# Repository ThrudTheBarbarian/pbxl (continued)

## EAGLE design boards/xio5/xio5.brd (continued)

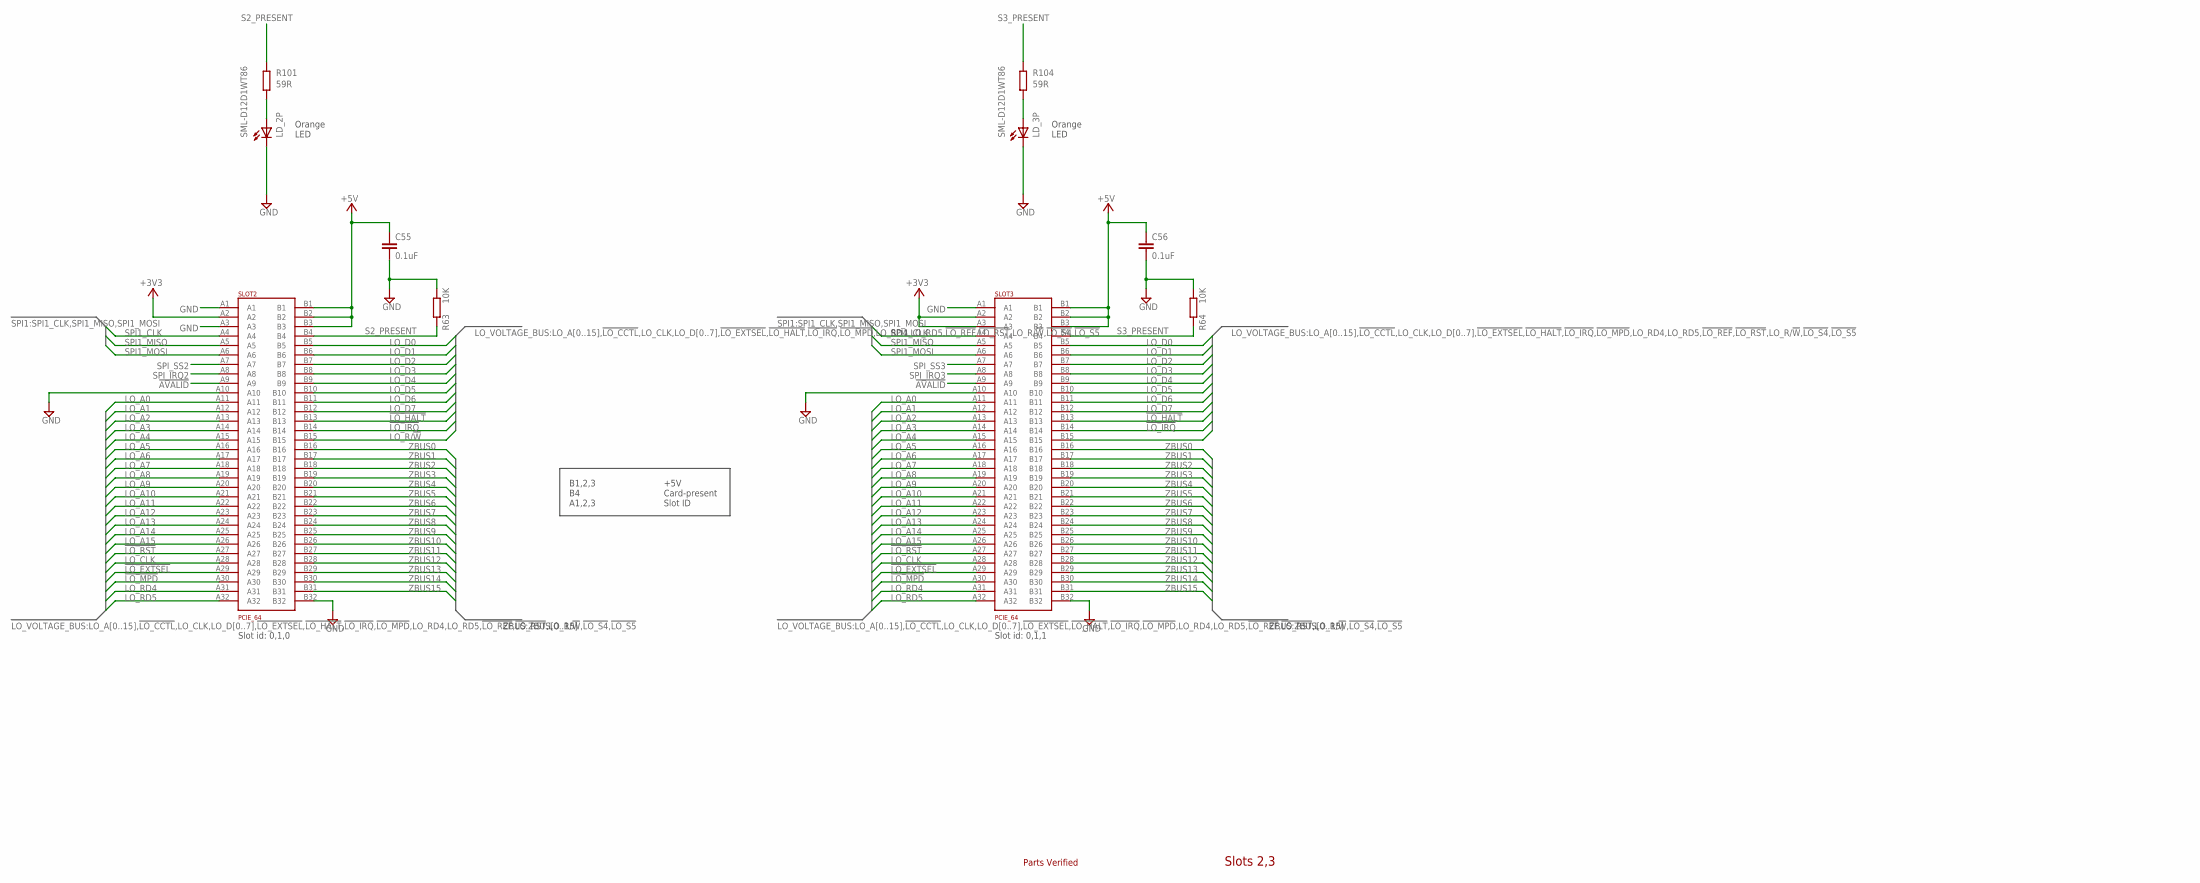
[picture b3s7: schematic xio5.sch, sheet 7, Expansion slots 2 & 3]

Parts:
C55, C56: 0.1uF; C0201
LD_2P, LD_3P: SML-D12D1WT86; CHIPLED_0603
R63, R64: 10K; R0201
R101, R104: 59R; R0402
SLOT2, SLOT3: PCIE_64; PCI-E_64

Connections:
!AVALID!: SLOT2.A9, SLOT3.A9; also elsewhere on the board
!LO_EXTSEL!: SLOT2.A29, SLOT3.A29; also elsewhere on the board
!LO_HALT!: SLOT2.B13, SLOT3.B13; also elsewhere on the board
!LO_IRQ!: SLOT2.B14, SLOT3.B14; also elsewhere on the board
!LO_MPD!: SLOT2.A30, SLOT3.A30; also elsewhere on the board
!LO_RST!: SLOT2.A27, SLOT3.A27; also elsewhere on the board
+3V3: SLOT2.A2, SLOT3.A2, SLOT3.A3; also elsewhere on the board
+5V: C55.1, C56.1, SLOT2.B1, SLOT2.B2, SLOT2.B3, SLOT3.B1, SLOT3.B2, SLOT3.B3; also elsewhere on the board
GND: C55.2, C56.2, LD_2P.C, LD_3P.C, R63.1, R64.1, SLOT2.A1, SLOT2.A3, SLOT2.A10, SLOT2.B32, SLOT3.A1, SLOT3.A10, SLOT3.B32; also elsewhere on the board
LO_A0: SLOT2.A11, SLOT3.A11; also elsewhere on the board
LO_A1: SLOT2.A12, SLOT3.A12; also elsewhere on the board
LO_A2: SLOT2.A13, SLOT3.A13; also elsewhere on the board
LO_A3: SLOT2.A14, SLOT3.A14; also elsewhere on the board
LO_A4: SLOT2.A15, SLOT3.A15; also elsewhere on the board
LO_A5: SLOT2.A16, SLOT3.A16; also elsewhere on the board
LO_A6: SLOT2.A17, SLOT3.A17; also elsewhere on the board
LO_A7: SLOT2.A18, SLOT3.A18; also elsewhere on the board
LO_A8: SLOT2.A19, SLOT3.A19; also elsewhere on the board
LO_A9: SLOT2.A20, SLOT3.A20; also elsewhere on the board
LO_A10: SLOT2.A21, SLOT3.A21; also elsewhere on the board
LO_A11: SLOT2.A22, SLOT3.A22; also elsewhere on the board
LO_A12: SLOT2.A23, SLOT3.A23; also elsewhere on the board
LO_A13: SLOT2.A24, SLOT3.A24; also elsewhere on the board
LO_A14: SLOT2.A25, SLOT3.A25; also elsewhere on the board
LO_A15: SLOT2.A26, SLOT3.A26; also elsewhere on the board
LO_CLK: SLOT2.A28, SLOT3.A28; also elsewhere on the board
LO_D0: SLOT2.B5, SLOT3.B5; also elsewhere on the board
LO_D1: SLOT2.B6, SLOT3.B6; also elsewhere on the board
LO_D2: SLOT2.B7, SLOT3.B7; also elsewhere on the board
LO_D3: SLOT2.B8, SLOT3.B8; also elsewhere on the board
LO_D4: SLOT2.B9, SLOT3.B9; also elsewhere on the board
LO_D5: SLOT2.B10, SLOT3.B10; also elsewhere on the board
LO_D6: SLOT2.B11, SLOT3.B11; also elsewhere on the board
LO_D7: SLOT2.B12, SLOT3.B12; also elsewhere on the board
LO_R/!W!: SLOT2.B15, SLOT3.B15; also elsewhere on the board
LO_RD4: SLOT2.A31, SLOT3.A31; also elsewhere on the board
LO_RD5: SLOT2.A32, SLOT3.A32; also elsewhere on the board
unnamed: LD_2P.A, R101.2
unnamed: LD_3P.A, R104.2
S2_PRESENT: R63.2, R101.1, SLOT2.B4; also elsewhere on the board
S3_PRESENT: R64.2, R104.1, SLOT3.B4; also elsewhere on the board
SPI1_CLK: SLOT2.A4, SLOT3.A4; also elsewhere on the board
SPI1_MISO: SLOT2.A5, SLOT3.A5; also elsewhere on the board
SPI1_MOSI: SLOT2.A6, SLOT3.A6; also elsewhere on the board
SPI_IRQ2: SLOT2.A8; also elsewhere on the board
SPI_IRQ3: SLOT3.A8; also elsewhere on the board
SPI_SS2: SLOT2.A7; also elsewhere on the board
SPI_SS3: SLOT3.A7; also elsewhere on the board
ZBUS0: SLOT2.B16, SLOT3.B16; also elsewhere on the board
ZBUS1: SLOT2.B17, SLOT3.B17; also elsewhere on the board
ZBUS2: SLOT2.B18, SLOT3.B18; also elsewhere on the board
ZBUS3: SLOT2.B19, SLOT3.B19; also elsewhere on the board
ZBUS4: SLOT2.B20, SLOT3.B20; also elsewhere on the board
ZBUS5: SLOT2.B21, SLOT3.B21; also elsewhere on the board
ZBUS6: SLOT2.B22, SLOT3.B22; also elsewhere on the board
ZBUS7: SLOT2.B23, SLOT3.B23; also elsewhere on the board
ZBUS8: SLOT2.B24, SLOT3.B24; also elsewhere on the board
ZBUS9: SLOT2.B25, SLOT3.B25; also elsewhere on the board
ZBUS10: SLOT2.B26, SLOT3.B26; also elsewhere on the board
ZBUS11: SLOT2.B27, SLOT3.B27; also elsewhere on the board
ZBUS12: SLOT2.B28, SLOT3.B28; also elsewhere on the board
ZBUS13: SLOT2.B29, SLOT3.B29; also elsewhere on the board
ZBUS14: SLOT2.B30, SLOT3.B30; also elsewhere on the board
ZBUS15: SLOT2.B31, SLOT3.B31; also elsewhere on the board

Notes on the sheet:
Slots 2,3
Slot id: 0,1,0
Slot id: 0,1,1
B1,2,3 B4 A1,2,3
+5V Card-present Slot ID
Orange LED
Parts Verified

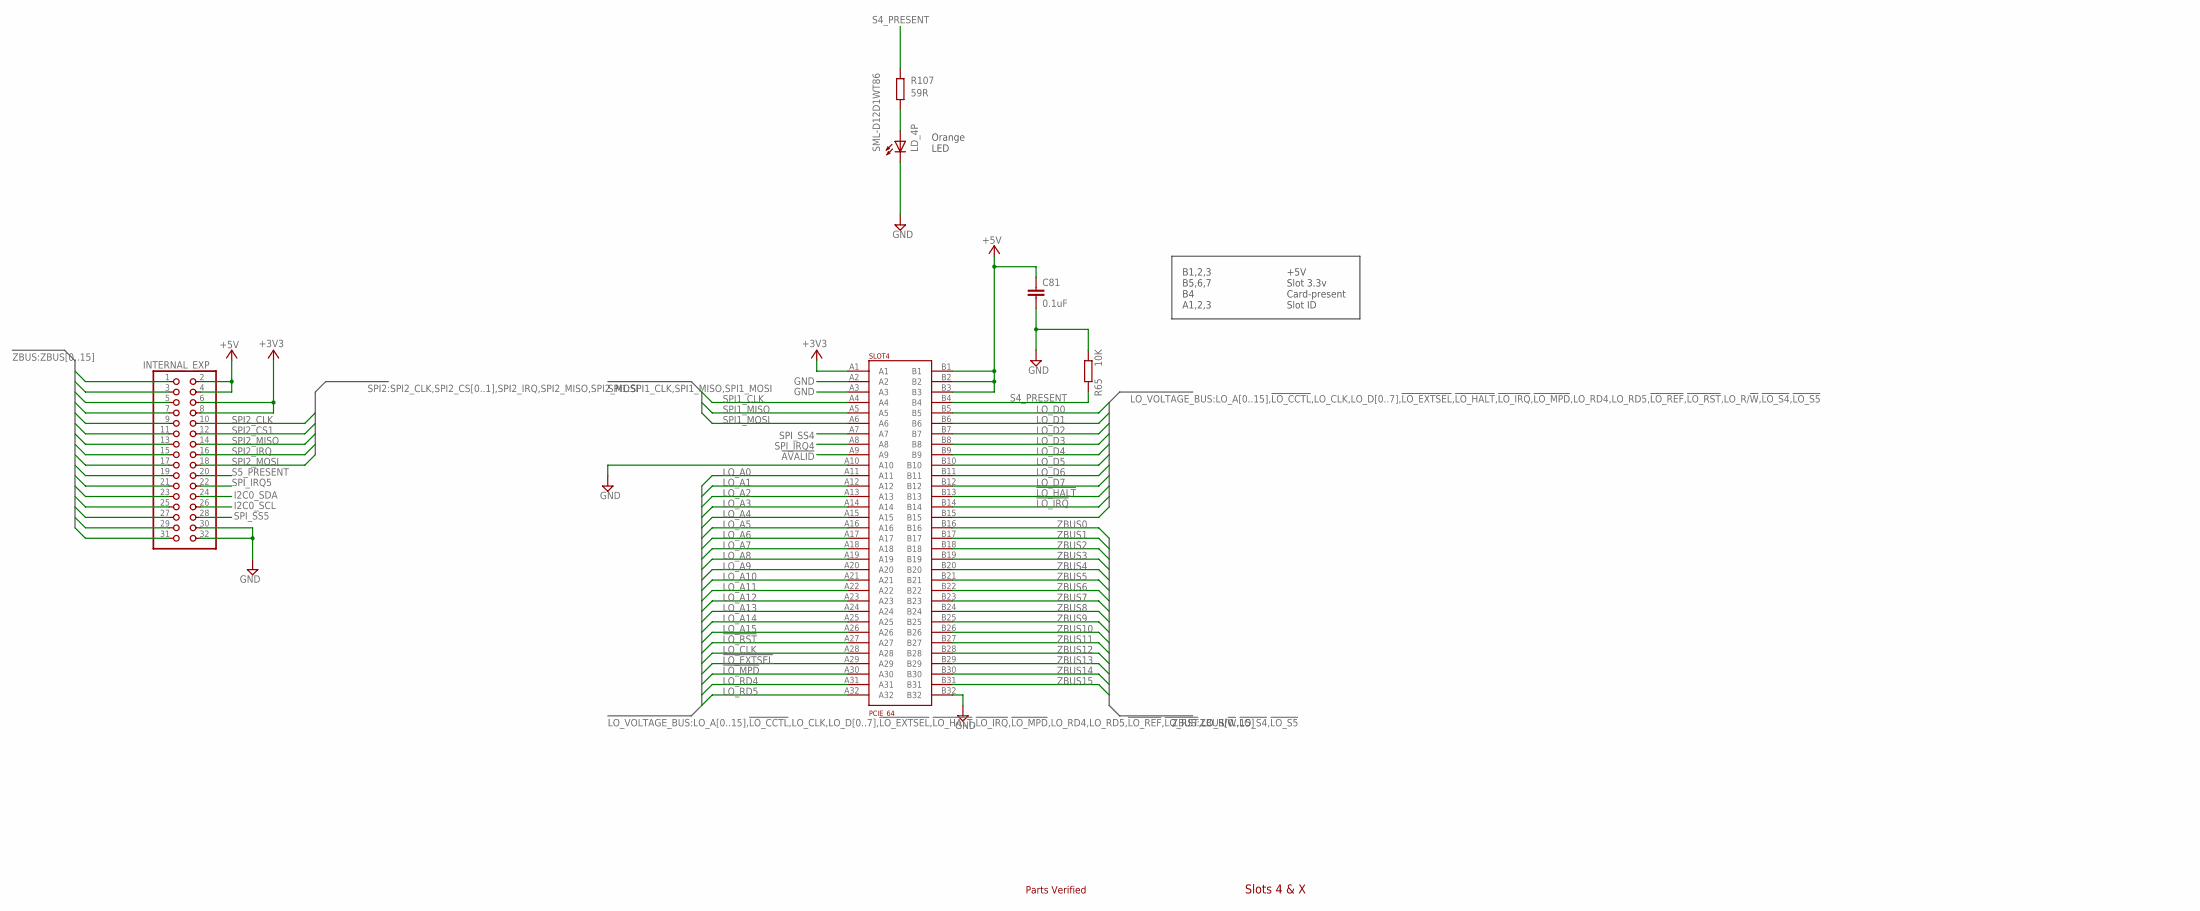
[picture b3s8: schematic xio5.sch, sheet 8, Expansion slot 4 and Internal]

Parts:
C81: 0.1uF; C0201
INTERNAL_EXP: PINHD-2X16_2.00; 2X16M
LD_4P: SML-D12D1WT86; CHIPLED_0603
R65: 10K; R0201
R107: 59R; R0402
SLOT4: PCIE_64; PCI-E_64

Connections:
!AVALID!: SLOT4.A9; also elsewhere on the board
!LO_EXTSEL!: SLOT4.A29; also elsewhere on the board
!LO_HALT!: SLOT4.B13; also elsewhere on the board
!LO_IRQ!: SLOT4.B14; also elsewhere on the board
!LO_MPD!: SLOT4.A30; also elsewhere on the board
!LO_RST!: SLOT4.A27; also elsewhere on the board
+3V3: INTERNAL_EXP.6, INTERNAL_EXP.8, SLOT4.A1; also elsewhere on the board
+5V: C81.1, INTERNAL_EXP.2, INTERNAL_EXP.4, SLOT4.B1, SLOT4.B2, SLOT4.B3; also elsewhere on the board
GND: C81.2, INTERNAL_EXP.30, INTERNAL_EXP.32, LD_4P.C, R65.1, SLOT4.A2, SLOT4.A3, SLOT4.A10, SLOT4.B32; also elsewhere on the board
I2C0_SCL: INTERNAL_EXP.26; also elsewhere on the board
I2C0_SDA: INTERNAL_EXP.24; also elsewhere on the board
LO_A0: SLOT4.A11; also elsewhere on the board
LO_A1: SLOT4.A12; also elsewhere on the board
LO_A2: SLOT4.A13; also elsewhere on the board
LO_A3: SLOT4.A14; also elsewhere on the board
LO_A4: SLOT4.A15; also elsewhere on the board
LO_A5: SLOT4.A16; also elsewhere on the board
LO_A6: SLOT4.A17; also elsewhere on the board
LO_A7: SLOT4.A18; also elsewhere on the board
LO_A8: SLOT4.A19; also elsewhere on the board
LO_A9: SLOT4.A20; also elsewhere on the board
LO_A10: SLOT4.A21; also elsewhere on the board
LO_A11: SLOT4.A22; also elsewhere on the board
LO_A12: SLOT4.A23; also elsewhere on the board
LO_A13: SLOT4.A24; also elsewhere on the board
LO_A14: SLOT4.A25; also elsewhere on the board
LO_A15: SLOT4.A26; also elsewhere on the board
LO_CLK: SLOT4.A28; also elsewhere on the board
LO_D0: SLOT4.B5; also elsewhere on the board
LO_D1: SLOT4.B6; also elsewhere on the board
LO_D2: SLOT4.B7; also elsewhere on the board
LO_D3: SLOT4.B8; also elsewhere on the board
LO_D4: SLOT4.B9; also elsewhere on the board
LO_D5: SLOT4.B10; also elsewhere on the board
LO_D6: SLOT4.B11; also elsewhere on the board
LO_D7: SLOT4.B12; also elsewhere on the board
LO_R/!W!: SLOT4.B15; also elsewhere on the board
LO_RD4: SLOT4.A31; also elsewhere on the board
LO_RD5: SLOT4.A32; also elsewhere on the board
unnamed: LD_4P.A, R107.2
S4_PRESENT: R65.2, R107.1, SLOT4.B4; also elsewhere on the board
S5_PRESENT: INTERNAL_EXP.20; also elsewhere on the board
SPI1_CLK: SLOT4.A4; also elsewhere on the board
SPI1_MISO: SLOT4.A5; also elsewhere on the board
SPI1_MOSI: SLOT4.A6; also elsewhere on the board
SPI2_CLK: INTERNAL_EXP.10; also elsewhere on the board
SPI2_CS1: INTERNAL_EXP.12; also elsewhere on the board
SPI2_IRQ: INTERNAL_EXP.16; also elsewhere on the board
SPI2_MISO: INTERNAL_EXP.14; also elsewhere on the board
SPI2_MOSI: INTERNAL_EXP.18; also elsewhere on the board
SPI_IRQ4: SLOT4.A8; also elsewhere on the board
SPI_IRQ5: INTERNAL_EXP.22; also elsewhere on the board
SPI_SS4: SLOT4.A7; also elsewhere on the board
SPI_SS5: INTERNAL_EXP.28; also elsewhere on the board
ZBUS0: INTERNAL_EXP.31, SLOT4.B16; also elsewhere on the board
ZBUS1: INTERNAL_EXP.29, SLOT4.B17; also elsewhere on the board
ZBUS2: INTERNAL_EXP.27, SLOT4.B18; also elsewhere on the board
ZBUS3: INTERNAL_EXP.25, SLOT4.B19; also elsewhere on the board
ZBUS4: INTERNAL_EXP.23, SLOT4.B20; also elsewhere on the board
ZBUS5: INTERNAL_EXP.21, SLOT4.B21; also elsewhere on the board
ZBUS6: INTERNAL_EXP.19, SLOT4.B22; also elsewhere on the board
ZBUS7: INTERNAL_EXP.17, SLOT4.B23; also elsewhere on the board
ZBUS8: INTERNAL_EXP.15, SLOT4.B24; also elsewhere on the board
ZBUS9: INTERNAL_EXP.13, SLOT4.B25; also elsewhere on the board
ZBUS10: INTERNAL_EXP.11, SLOT4.B26; also elsewhere on the board
ZBUS11: INTERNAL_EXP.9, SLOT4.B27; also elsewhere on the board
ZBUS12: INTERNAL_EXP.7, SLOT4.B28; also elsewhere on the board
ZBUS13: INTERNAL_EXP.5, SLOT4.B29; also elsewhere on the board
ZBUS14: INTERNAL_EXP.3, SLOT4.B30; also elsewhere on the board
ZBUS15: INTERNAL_EXP.1, SLOT4.B31; also elsewhere on the board

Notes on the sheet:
Slots 4 & X
B1,2,3 B5,6,7 B4 A1,2,3
+5V Slot 3.3v Card-present Slot ID
Orange LED
Parts Verified

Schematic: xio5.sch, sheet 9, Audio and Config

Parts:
AUDIO_CONN: PINHD-2X06_2.00; 2X06M
R7, R8, R9, R11, R12, R14, R18, R20: 10K; R0201
SW_CONFIG: SW_DIP-8; DIPSWITCH-08
ZTURN: ZTURN

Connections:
+3V3: AUDIO_CONN.7, R7.2, R8.2, R9.2, R11.2, R12.2, R14.2, R18.2, R20.2; also elsewhere on the board
+5V: AUDIO_CONN.5; also elsewhere on the board
CFG0: R14.1, SW_CONFIG.1; also elsewhere on the board
CFG1: R12.1, SW_CONFIG.2; also elsewhere on the board
CFG2: R11.1, SW_CONFIG.3; also elsewhere on the board
CFG3: R9.1, SW_CONFIG.4; also elsewhere on the board
CFG4: R8.1, SW_CONFIG.5; also elsewhere on the board
CFG5: R7.1, SW_CONFIG.6; also elsewhere on the board
CFG6: R18.1, SW_CONFIG.7; also elsewhere on the board
CFG7: R20.1, SW_CONFIG.8; also elsewhere on the board
GND: AUDIO_CONN.4, AUDIO_CONN.9, AUDIO_CONN.11, SW_CONFIG.9, SW_CONFIG.10, SW_CONFIG.11, SW_CONFIG.12, SW_CONFIG.13, SW_CONFIG.14, SW_CONFIG.15, SW_CONFIG.16; also elsewhere on the board
I2C0_SCL: AUDIO_CONN.1, ZTURN.CN1_78 (I2C0_SCL); also elsewhere on the board
I2C0_SDA: AUDIO_CONN.3, ZTURN.CN1_76 (I2C0_SDA); also elsewhere on the board
unnamed: AUDIO_CONN.2, ZTURN.CN1_71 (I2S_SCLK)
unnamed: AUDIO_CONN.12, ZTURN.CN1_72 (I2S_FSYNC_OUT)
unnamed: AUDIO_CONN.10, ZTURN.CN1_74 (I2S_DOUT)
unnamed: AUDIO_CONN.8, ZTURN.CN1_73 (I2S_FSYNC_IN)
unnamed: AUDIO_CONN.6, ZTURN.CN1_75 (I2S_DIN)

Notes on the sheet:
Audio and config
Parts Verified

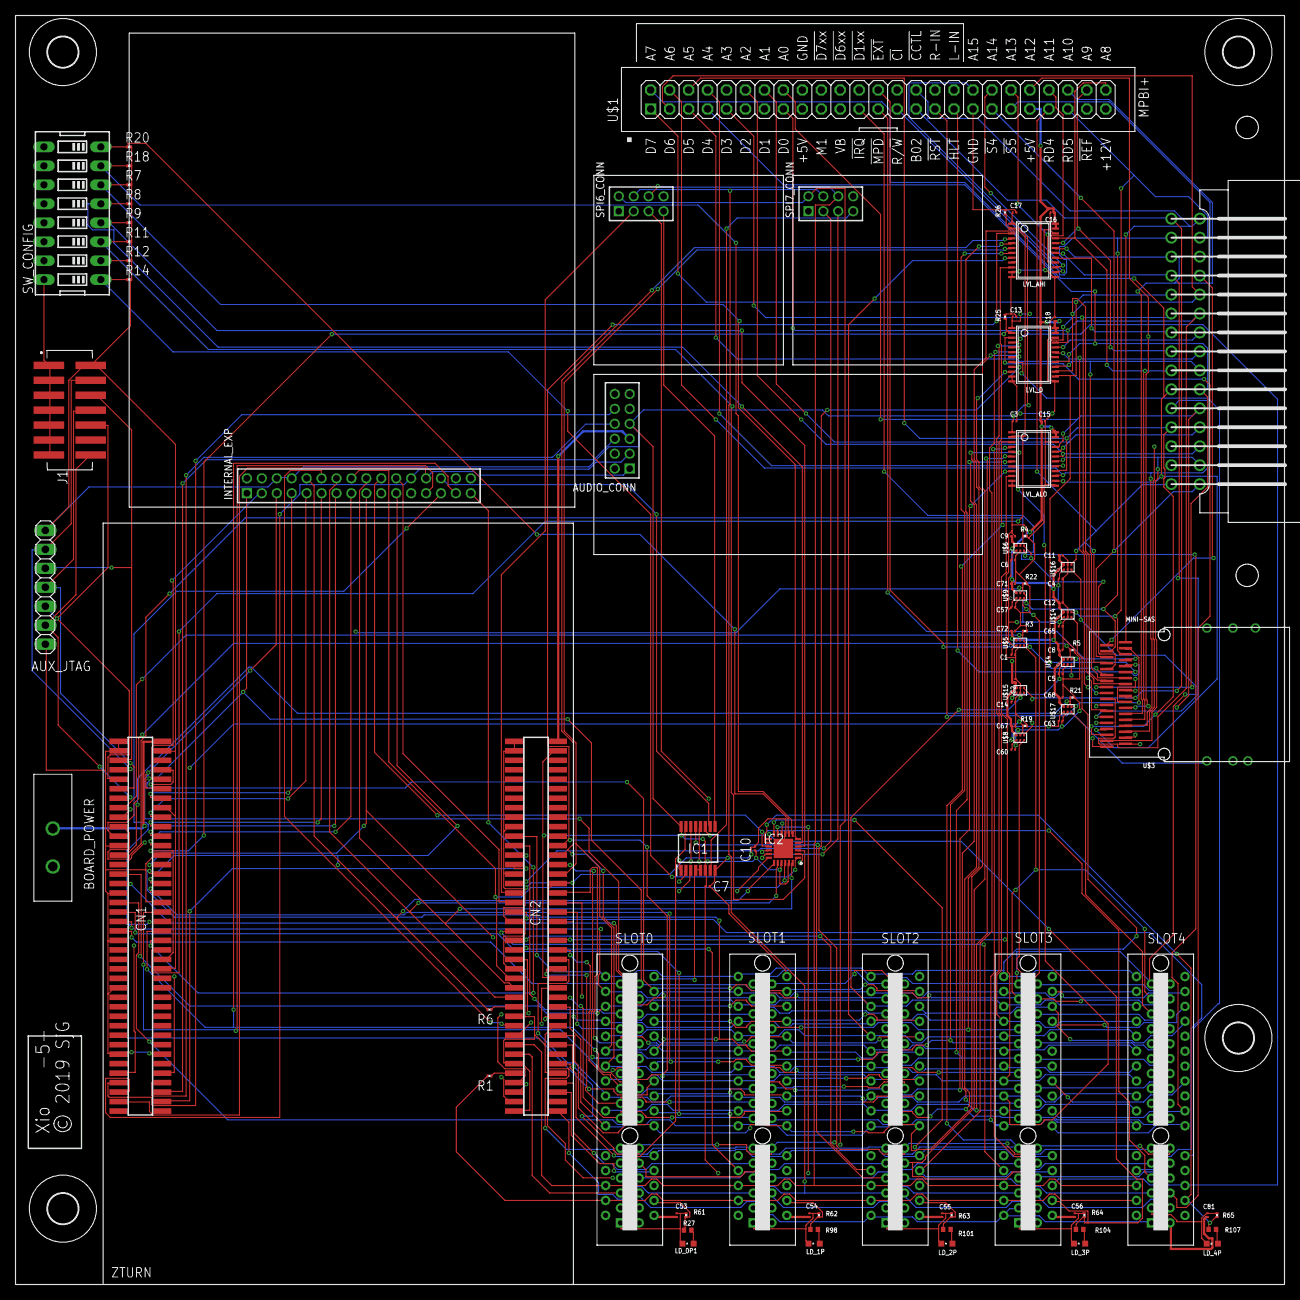
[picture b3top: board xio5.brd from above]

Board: 6 copper layers, 170.0 x 170.0 mm, 99 parts (0 on the bottom side), 161 nets.

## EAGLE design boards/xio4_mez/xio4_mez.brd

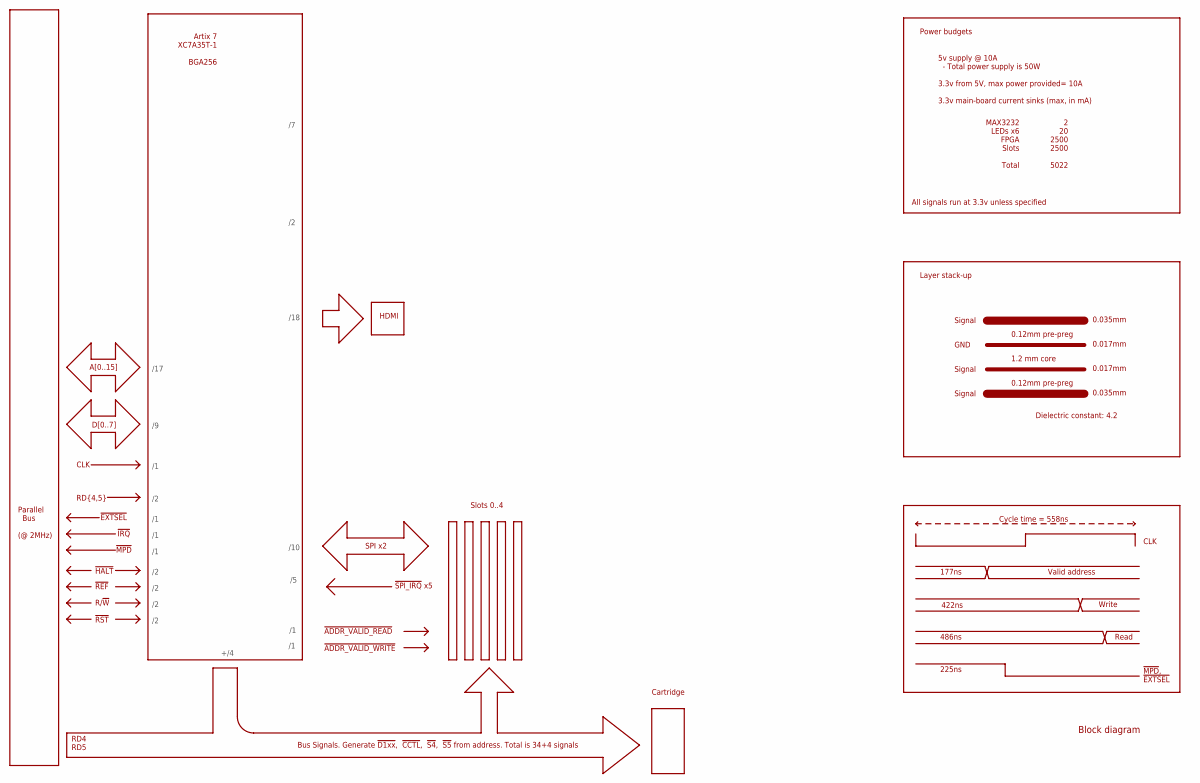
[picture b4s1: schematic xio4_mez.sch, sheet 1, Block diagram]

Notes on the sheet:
Slots 0..4
Bus Signals. Generate !D1xx!, !CCTL!, !S4!, !S5! from address. Total is 34+4 signals
5v supply @ 10A - Total power supply is 50W 3.3v from 5V, max power provided= 10A 3.3v main-board current sinks (max, in mA)
MAX3232 LEDs x6 FPGA Slots Total
2 20 2500 2500 5022
1.2 mm core
0.12mm pre-preg
0.035mm
0.017mm
Layer stack-up
GND
Dielectric constant: 4.2
Cycle time = 558ns
Valid address
Write
Read
177ns
422ns
486ns
225ns
!MPD!, !EXTSEL!
CLK
Power budgets
Artix 7 XC7A35T-1 BGA256
HDMI
Signal
Block diagram
Parallel Bus (@ 2MHz)
A[0..15]
D[0..7]
RD{4,5}
!MPD!
!IRQ!
!EXTSEL!
!HALT!
!REF!
R/!W!
/17
!ADDR_VALID_READ!
!ADDR_VALID_WRITE!

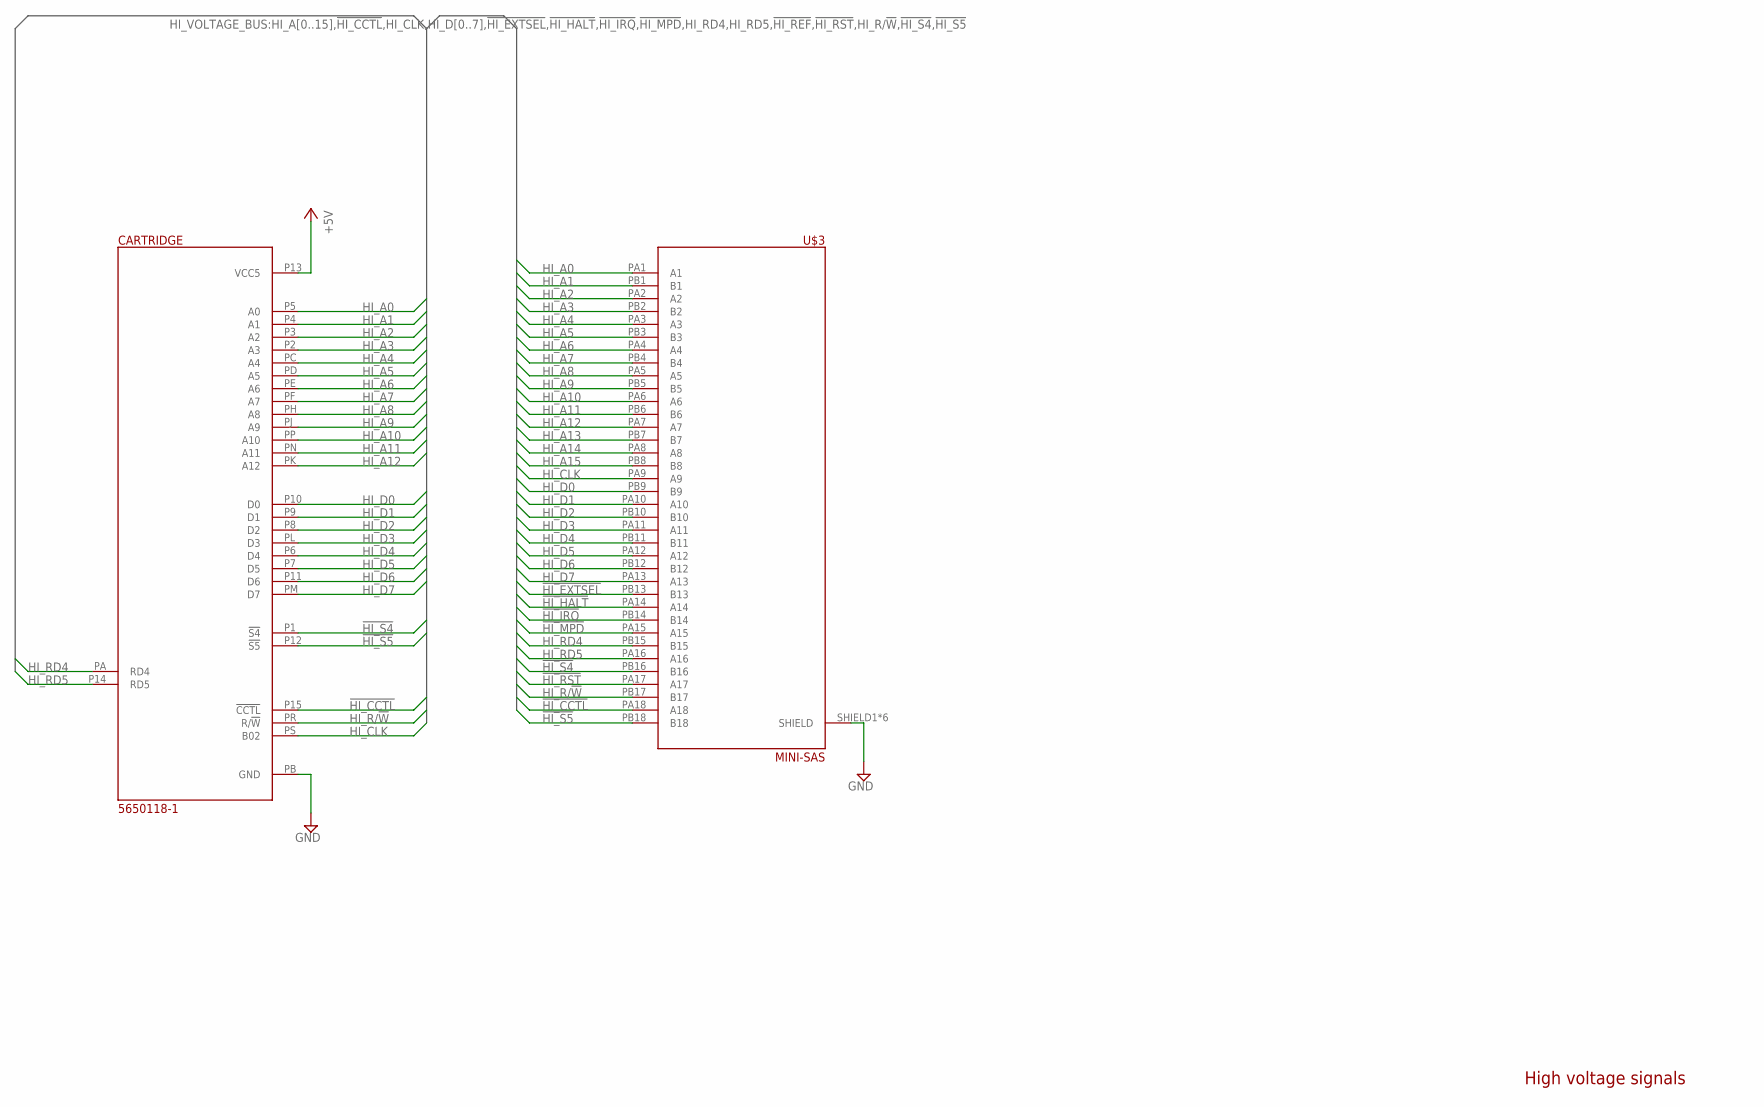
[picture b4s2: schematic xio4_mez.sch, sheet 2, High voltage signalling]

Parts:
CARTRIDGE: 5650118-1; A8_CART
U$3: MINI-SAS

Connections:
!HI_CCTL!: CARTRIDGE.P15 (!CCTL!), U$3.PA18 (A18)
!HI_EXTSEL!: U$3.PB13 (B13); also elsewhere on the board
!HI_HALT!: U$3.PA14 (A14); also elsewhere on the board
!HI_IRQ!: U$3.PB14 (B14); also elsewhere on the board
!HI_MPD!: U$3.PA15 (A15); also elsewhere on the board
!HI_RST!: U$3.PA17 (A17); also elsewhere on the board
!HI_S4!: CARTRIDGE.P1 (!S4!), U$3.PB16 (B16)
!HI_S5!: CARTRIDGE.P12 (!S5!), U$3.PB18 (B18)
+5V: CARTRIDGE.P13 (VCC5); also elsewhere on the board
GND: CARTRIDGE.PB (GND), U$3.SHIELD1 (SHIELD), U$3.SHIELD2 (SHIELD), U$3.SHIELD3 (SHIELD), U$3.SHIELD4 (SHIELD), U$3.SHIELD5 (SHIELD), U$3.SHIELD6 (SHIELD); also elsewhere on the board
HI_A0: CARTRIDGE.P5 (A0), U$3.PA1 (A1); also elsewhere on the board
HI_A1: CARTRIDGE.P4 (A1), U$3.PB1 (B1); also elsewhere on the board
HI_A2: CARTRIDGE.P3 (A2), U$3.PA2 (A2); also elsewhere on the board
HI_A3: CARTRIDGE.P2 (A3), U$3.PB2 (B2); also elsewhere on the board
HI_A4: CARTRIDGE.PC (A4), U$3.PA3 (A3); also elsewhere on the board
HI_A5: CARTRIDGE.PD (A5), U$3.PB3 (B3); also elsewhere on the board
HI_A6: CARTRIDGE.PE (A6), U$3.PA4 (A4); also elsewhere on the board
HI_A7: CARTRIDGE.PF (A7), U$3.PB4 (B4); also elsewhere on the board
HI_A8: CARTRIDGE.PH (A8), U$3.PA5 (A5); also elsewhere on the board
HI_A9: CARTRIDGE.PJ (A9), U$3.PB5 (B5); also elsewhere on the board
HI_A10: CARTRIDGE.PP (A10), U$3.PA6 (A6); also elsewhere on the board
HI_A11: CARTRIDGE.PN (A11), U$3.PB6 (B6); also elsewhere on the board
HI_A12: CARTRIDGE.PK (A12), U$3.PA7 (A7); also elsewhere on the board
HI_A13: U$3.PB7 (B7); also elsewhere on the board
HI_A14: U$3.PA8 (A8); also elsewhere on the board
HI_A15: U$3.PB8 (B8); also elsewhere on the board
HI_CLK: CARTRIDGE.PS (B02), U$3.PA9 (A9); also elsewhere on the board
HI_D0: CARTRIDGE.P10 (D0), U$3.PB9 (B9); also elsewhere on the board
HI_D1: CARTRIDGE.P9 (D1), U$3.PA10 (A10); also elsewhere on the board
HI_D2: CARTRIDGE.P8 (D2), U$3.PB10 (B10); also elsewhere on the board
HI_D3: CARTRIDGE.PL (D3), U$3.PA11 (A11); also elsewhere on the board
HI_D4: CARTRIDGE.P6 (D4), U$3.PB11 (B11); also elsewhere on the board
HI_D5: CARTRIDGE.P7 (D5), U$3.PA12 (A12); also elsewhere on the board
HI_D6: CARTRIDGE.P11 (D6), U$3.PB12 (B12); also elsewhere on the board
HI_D7: CARTRIDGE.PM (D7), U$3.PA13 (A13); also elsewhere on the board
HI_R/!W!: CARTRIDGE.PR (R/!W!), U$3.PB17 (B17); also elsewhere on the board
HI_RD4: CARTRIDGE.PA (RD4), U$3.PB15 (B15); also elsewhere on the board
HI_RD5: CARTRIDGE.P14 (RD5), U$3.PA16 (A16); also elsewhere on the board

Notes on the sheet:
High voltage signals

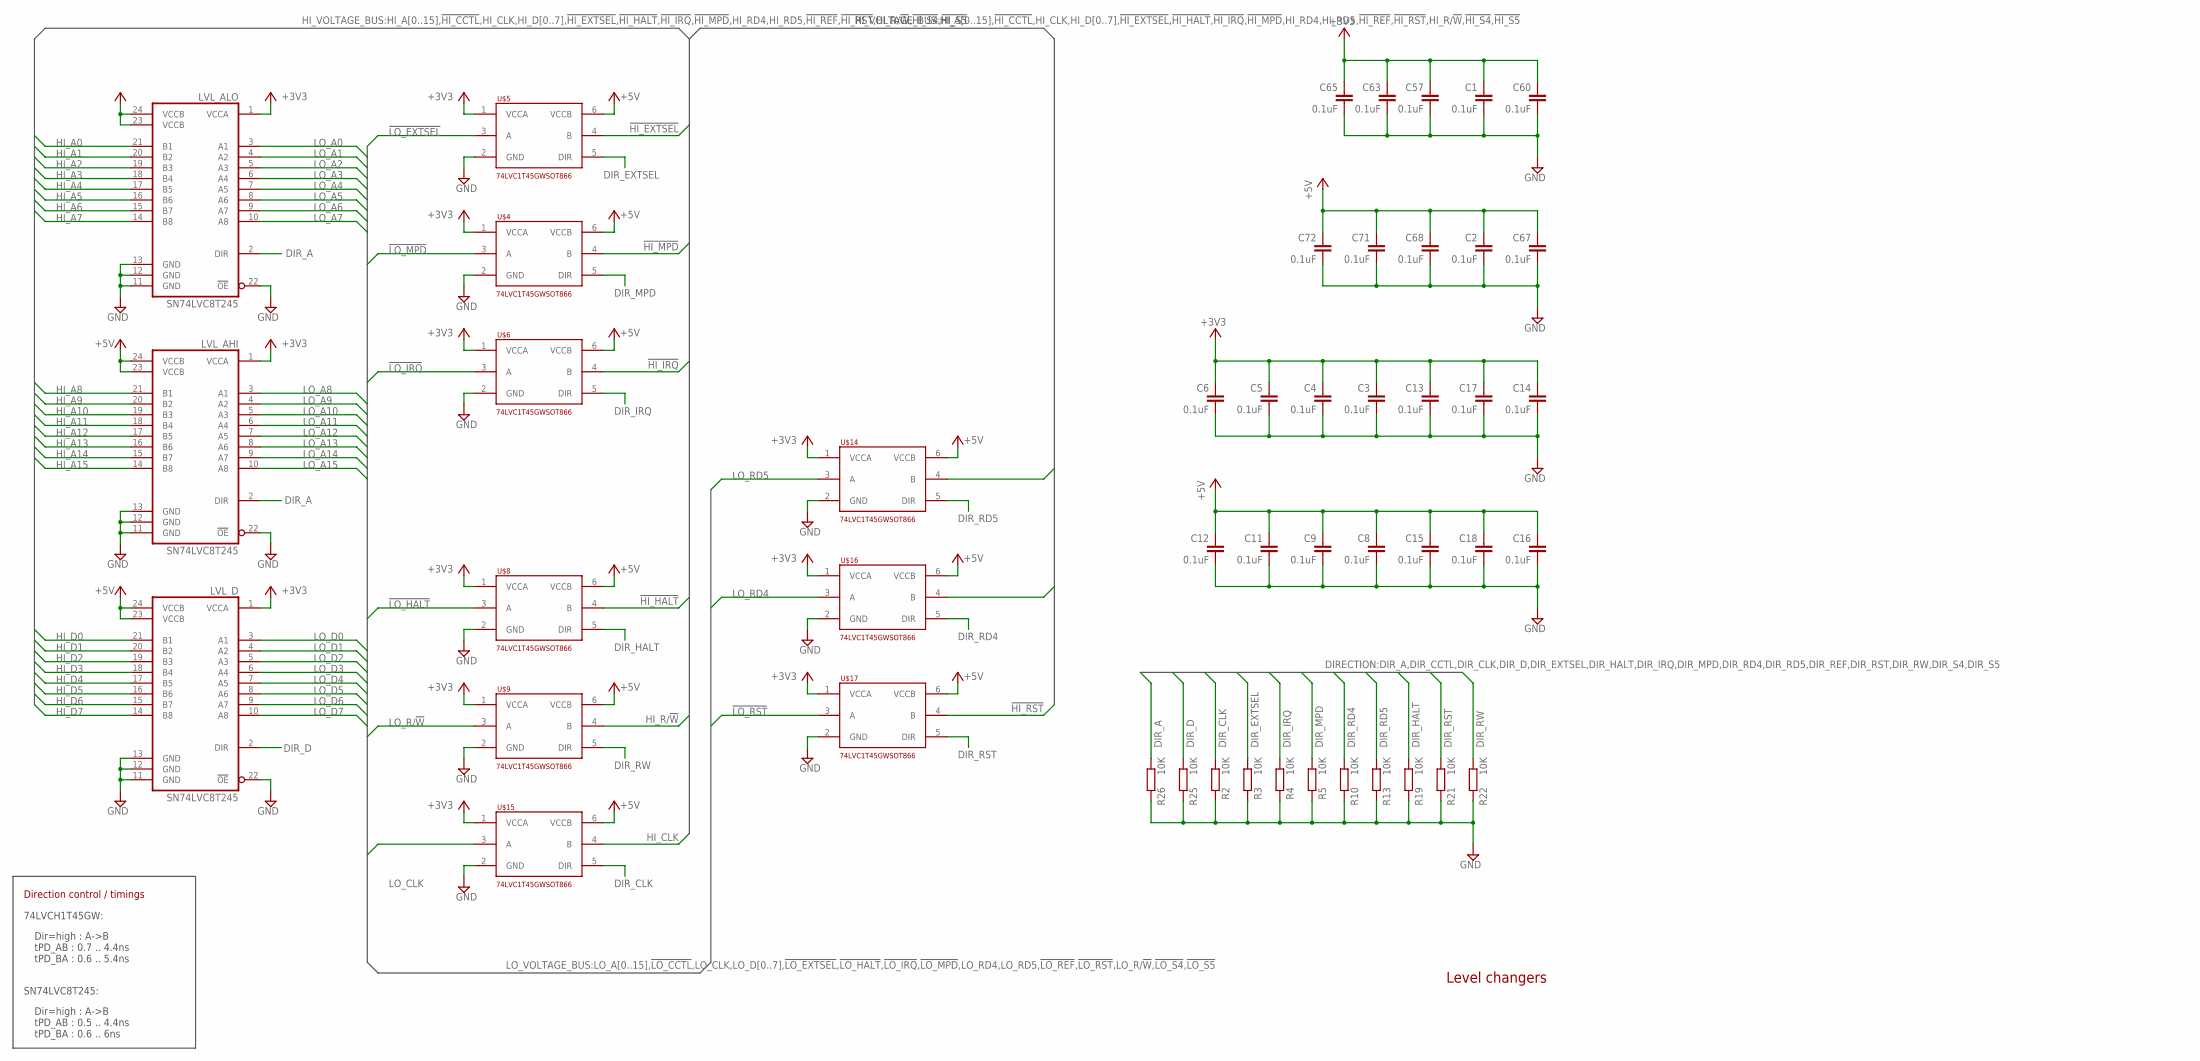
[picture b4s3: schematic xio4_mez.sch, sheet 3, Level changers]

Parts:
C1, C2, C3, C4, C5, C6, C8, C9, C11, C12, C13, C14, C15, C16, C17, C18, C57, C60, C63, C65, C67, C68, C71, C72: 0.1uF; C0201
LVL_AHI: SN74LVC8T245; TSSOP24
LVL_ALO: SN74LVC8T245; TSSOP24
LVL_D: SN74LVC8T245; TSSOP24
R2, R3, R4, R5, R10, R13, R19, R21, R22, R25, R26: 10K; R0201
U$4, U$5, U$6, U$8, U$9, U$14, U$15, U$16, U$17: 74LVC1T45GWSOT866; SOT886

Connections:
!HI_EXTSEL!: U$5.4 (B); also elsewhere on the board
!HI_HALT!: U$8.4 (B); also elsewhere on the board
!HI_IRQ!: U$6.4 (B); also elsewhere on the board
!HI_MPD!: U$4.4 (B); also elsewhere on the board
!HI_RST!: U$17.4 (B); also elsewhere on the board
!LO_EXTSEL!: U$5.3 (A); also elsewhere on the board
!LO_HALT!: U$8.3 (A); also elsewhere on the board
!LO_IRQ!: U$6.3 (A); also elsewhere on the board
!LO_MPD!: U$4.3 (A); also elsewhere on the board
!LO_RST!: U$17.3 (A); also elsewhere on the board
+3V3: C1.1, C3.1, C4.1, C5.1, C6.1, C13.1, C14.1, C17.1, C57.1, C60.1, C63.1, C65.1, LVL_AHI.1 (VCCA), LVL_ALO.1 (VCCA), LVL_D.1 (VCCA), U$4.1 (VCCA), U$5.1 (VCCA), U$6.1 (VCCA), U$8.1 (VCCA), U$9.1 (VCCA), U$14.1 (VCCA), U$15.1 (VCCA), U$16.1 (VCCA), U$17.1 (VCCA)
+5V: C2.1, C8.1, C9.1, C11.1, C12.1, C15.1, C16.1, C18.1, C67.1, C68.1, C71.1, C72.1, LVL_AHI.23 (VCCB), LVL_AHI.24 (VCCB), LVL_ALO.23 (VCCB), LVL_ALO.24 (VCCB), LVL_D.23 (VCCB), LVL_D.24 (VCCB), U$4.6 (VCCB), U$5.6 (VCCB), U$6.6 (VCCB), U$8.6 (VCCB), U$9.6 (VCCB), U$14.6 (VCCB), U$15.6 (VCCB), U$16.6 (VCCB), U$17.6 (VCCB); also elsewhere on the board
DIR_A: LVL_AHI.2 (DIR), LVL_ALO.2 (DIR), R26.1; also elsewhere on the board
DIR_CLK: R2.1, U$15.5 (DIR); also elsewhere on the board
DIR_D: LVL_D.2 (DIR), R25.1; also elsewhere on the board
DIR_EXTSEL: R3.1, U$5.5 (DIR); also elsewhere on the board
DIR_HALT: R19.1, U$8.5 (DIR); also elsewhere on the board
DIR_IRQ: R4.1, U$6.5 (DIR); also elsewhere on the board
DIR_MPD: R5.1, U$4.5 (DIR); also elsewhere on the board
DIR_RD4: R10.1, U$16.5 (DIR); also elsewhere on the board
DIR_RD5: R13.1, U$14.5 (DIR); also elsewhere on the board
DIR_RST: R21.1, U$17.5 (DIR); also elsewhere on the board
DIR_RW: R22.1, U$9.5 (DIR); also elsewhere on the board
GND: C1.2, C2.2, C3.2, C4.2, C5.2, C6.2, C8.2, C9.2, C11.2, C12.2, C13.2, C14.2, C15.2, C16.2, C17.2, C18.2, C57.2, C60.2, C63.2, C65.2, C67.2, C68.2, C71.2, C72.2, LVL_AHI.11 (GND), LVL_AHI.12 (GND), LVL_AHI.13 (GND), LVL_AHI.22 (!OE!), LVL_ALO.11 (GND), LVL_ALO.12 (GND), LVL_ALO.13 (GND), LVL_ALO.22 (!OE!), LVL_D.11 (GND), LVL_D.12 (GND), LVL_D.13 (GND), LVL_D.22 (!OE!), R2.2, R3.2, R4.2, R5.2, R10.2, R13.2, R19.2, R21.2, R22.2, R25.2, R26.2, U$4.2 (GND), U$5.2 (GND), U$6.2 (GND), U$8.2 (GND), U$9.2 (GND), U$14.2 (GND), U$15.2 (GND), U$16.2 (GND), U$17.2 (GND); also elsewhere on the board
HI_A0: LVL_ALO.21 (B1); also elsewhere on the board
HI_A1: LVL_ALO.20 (B2); also elsewhere on the board
HI_A2: LVL_ALO.19 (B3); also elsewhere on the board
HI_A3: LVL_ALO.18 (B4); also elsewhere on the board
HI_A4: LVL_ALO.17 (B5); also elsewhere on the board
HI_A5: LVL_ALO.16 (B6); also elsewhere on the board
HI_A6: LVL_ALO.15 (B7); also elsewhere on the board
HI_A7: LVL_ALO.14 (B8); also elsewhere on the board
HI_A8: LVL_AHI.21 (B1); also elsewhere on the board
HI_A9: LVL_AHI.20 (B2); also elsewhere on the board
HI_A10: LVL_AHI.19 (B3); also elsewhere on the board
HI_A11: LVL_AHI.18 (B4); also elsewhere on the board
HI_A12: LVL_AHI.17 (B5); also elsewhere on the board
HI_A13: LVL_AHI.16 (B6); also elsewhere on the board
HI_A14: LVL_AHI.15 (B7); also elsewhere on the board
HI_A15: LVL_AHI.14 (B8); also elsewhere on the board
HI_CLK: U$15.4 (B); also elsewhere on the board
HI_D0: LVL_D.21 (B1); also elsewhere on the board
HI_D1: LVL_D.20 (B2); also elsewhere on the board
HI_D2: LVL_D.19 (B3); also elsewhere on the board
HI_D3: LVL_D.18 (B4); also elsewhere on the board
HI_D4: LVL_D.17 (B5); also elsewhere on the board
HI_D5: LVL_D.16 (B6); also elsewhere on the board
HI_D6: LVL_D.15 (B7); also elsewhere on the board
HI_D7: LVL_D.14 (B8); also elsewhere on the board
HI_R/!W!: U$9.4 (B); also elsewhere on the board
HI_RD4: U$16.4 (B); also elsewhere on the board
HI_RD5: U$14.4 (B); also elsewhere on the board
LO_A0: LVL_ALO.3 (A1); also elsewhere on the board
LO_A1: LVL_ALO.4 (A2); also elsewhere on the board
LO_A2: LVL_ALO.5 (A3); also elsewhere on the board
LO_A3: LVL_ALO.6 (A4); also elsewhere on the board
LO_A4: LVL_ALO.7 (A5); also elsewhere on the board
LO_A5: LVL_ALO.8 (A6); also elsewhere on the board
LO_A6: LVL_ALO.9 (A7); also elsewhere on the board
LO_A7: LVL_ALO.10 (A8); also elsewhere on the board
LO_A8: LVL_AHI.3 (A1); also elsewhere on the board
LO_A9: LVL_AHI.4 (A2); also elsewhere on the board
LO_A10: LVL_AHI.5 (A3); also elsewhere on the board
LO_A11: LVL_AHI.6 (A4); also elsewhere on the board
LO_A12: LVL_AHI.7 (A5); also elsewhere on the board
LO_A13: LVL_AHI.8 (A6); also elsewhere on the board
LO_A14: LVL_AHI.9 (A7); also elsewhere on the board
LO_A15: LVL_AHI.10 (A8); also elsewhere on the board
LO_CLK: U$15.3 (A); also elsewhere on the board
LO_D0: LVL_D.3 (A1); also elsewhere on the board
LO_D1: LVL_D.4 (A2); also elsewhere on the board
LO_D2: LVL_D.5 (A3); also elsewhere on the board
LO_D3: LVL_D.6 (A4); also elsewhere on the board
LO_D4: LVL_D.7 (A5); also elsewhere on the board
LO_D5: LVL_D.8 (A6); also elsewhere on the board
LO_D6: LVL_D.9 (A7); also elsewhere on the board
LO_D7: LVL_D.10 (A8); also elsewhere on the board
LO_R/!W!: U$9.3 (A); also elsewhere on the board
LO_RD4: U$16.3 (A); also elsewhere on the board
LO_RD5: U$14.3 (A); also elsewhere on the board

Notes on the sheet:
Dir=high : A->B tPD_AB : 0.7 .. 4.4ns tPD_BA : 0.6 .. 5.4ns
74LVCH1T45GW:
SN74LVC8T245:
Dir=high : A->B tPD_AB : 0.5 .. 4.4ns tPD_BA : 0.6 .. 6ns
Direction control / timings
Level changers
